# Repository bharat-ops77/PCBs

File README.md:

# Zero Voltage Switching Circuit

This is an LC tank oscillator circuit which uses two mosfets to feed the damping power to the LC tank...and use the output waveform to drive a High voltage transformer or an Induction heating coil.

---

## Repository Structure

```
├── docs/                   # Datasheet IRFP4468PbF n-channel MOSFET
├── manufacturing/          # Gerbers & BOM
│   ├── gerbers/            # Gerber and drill files for PCB fabrication
│   ├── bom/                # Bill of Materials (.csv )
├── ZVS.kicad_pcb  # KiCad PCB Layout file
├── ZVS.kicad_sch  # KiCad Schematic file
├── ZVS.kicad_pro  # KiCad Project file
└── README.md               # This file
 #Zero Voltage Switching (ZVS) Flyback Driver/Induction Heater
 ```
 This repository contains a KiCad schematic and PCB design for a high-efficiency Mazzilli Zero Voltage Switching (ZVS) Driver. This circuit is widely used for driving high-voltage transformers (like television flybacks), induction heaters, and Tesla coils due to its simplicity, high efficiency, and minimal thermal generation.
 
## **Features**:
  
  Zero Voltage Switching: The MOSFETs switch states only when the voltage across them drops to zero, drastically reducing switching losses and keeping the transistors cool.High-Current Handling: Utilizes heavy-duty IRFP4468PbF N-channel MOSFETs.Robust Gate Protection: Features dual $ Zener diodes and  pull-up resistors to prevent gate overvoltage and ensure rapid switching.
  
## **Circuit Overview & Operating Principle**:
  
  The circuit operates as a self-resonant push-pull oscillator. When power is applied via terminal J1, one MOSFET turns on slightly faster than the other. This imbalances the circuit, initiating a resonant oscillation between the parallel tank capacitors (C1 and C2) and the primary coil of the external transformer connected to J2.The fast diodes (D1 and D2) cross-couple the drains to the opposite gates, turning off one MOSFET as the other's drain voltage drops to zero.Resonant FrequencyThe operational frequency is determined solely by the total tank capacitance and the inductance of the external primary coil you attach to terminal Note: The inductors L1 and L2  act as DC chokes to smooth incoming current and do not affect the resonance frequency. Ensure your power supply can source substantial current  or more depending on your load).PCB Trace Widths: If you are routing this board, ensure the high-current paths (Power -> Input-> Chokes ->MOSFET-> Drains-> Tank ->Capacitors->Output) use very wide traces, thick copper  preferred), or are reinforced with soldered wire.Tank Capacitors: Do not use standard ceramic or cheap film capacitors for C1 and C2. The high ripple currents will quickly overheat and destroy them. Use dedicated resonant induction/MKP capacitors.Thermal Management: Even though ZVS minimizes heat, the MOSFETs will still warm up under continuous high loads. Mount both Q1 and Q2 to substantial heatsinks (isolated with mica/silicone pads if sharing a single heatsink).

## PCB Design:

   The PCB for this build is a two layer top and bottom , and uses through hole components for soldering simplicity.

## 3D Model:
### Rendered 3D Model:

### Bare PCB Front(1st Layer):  

### Bare PCB Rear(2nd Layer):  

## ⚠️WARNING:
  
  This circuit is designed to drive high-voltage/high-power components. Depending on the transformer connected to J2, it is capable of generating lethal voltages and currents. Always discharge capacitors before handling the circuit, work in a well-ventilated space, use appropriate personal protective equipment (PPE), and never operate the system unattended. The authors are not responsible for any damage, injury, or loss caused by the construction or operation of this project.
  
## 📄License:
  
  This project is open-source. Feel free to modify, distribute, and use it for your own applications under the GNU License.

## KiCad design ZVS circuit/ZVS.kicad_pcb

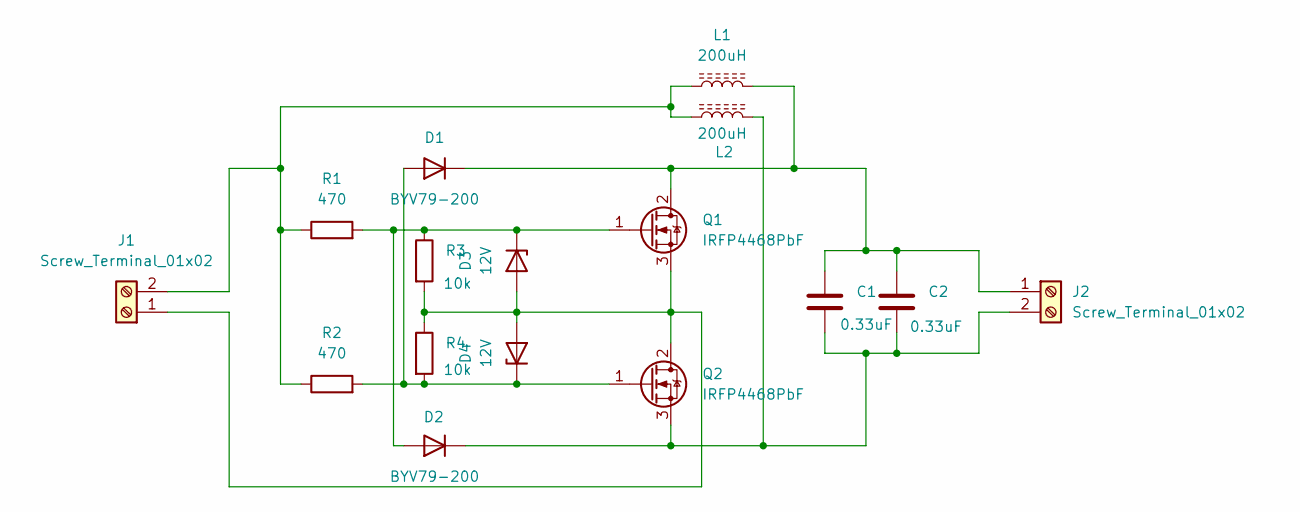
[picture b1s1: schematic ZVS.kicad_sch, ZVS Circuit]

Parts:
C1, C2: 0.33uF; C_Rect_L7.2mm_W3.0mm_P5.00mm_FKS2_FKP2_MKS2_MKP2
D1, D2: BYV79-200; TO-220-2_Vertical
D3, D4: 12V; D_A-405_P7.62mm_Horizontal
J1, J2: Screw_Terminal_01x02; TerminalBlock_MaiXu_MX126-5.0-02P_1x02_P5.00mm
L1, L2: 200uH; L_Radial_D13.5mm_P7.00mm_Fastron_09HCP
Q1, Q2: IRFP4468PbF; TO-247-3_Vertical
R1, R2: 470; R_Axial_DIN0922_L20.0mm_D9.0mm_P30.48mm_Horizontal
R3, R4: 10k; R_Axial_DIN0922_L20.0mm_D9.0mm_P30.48mm_Horizontal

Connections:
unnamed: D1.2 (A), D4.1 (K), Q2.1 (G), R2.2, R4.2
unnamed: C1.1, C2.1, D1.1 (K), J2.1, L1.2, Q1.2 (D)
unnamed: D2.2 (A), D3.1 (K), Q1.1 (G), R1.2, R3.1
unnamed: C1.2, C2.2, D2.1 (K), J2.2, L2.2, Q2.3 (S)
unnamed: D3.2 (A), D4.2 (A), J1.1, Q1.3 (S), Q2.2 (D), R3.2, R4.1
unnamed: J1.2, L1.1, L2.1, R1.1, R2.1

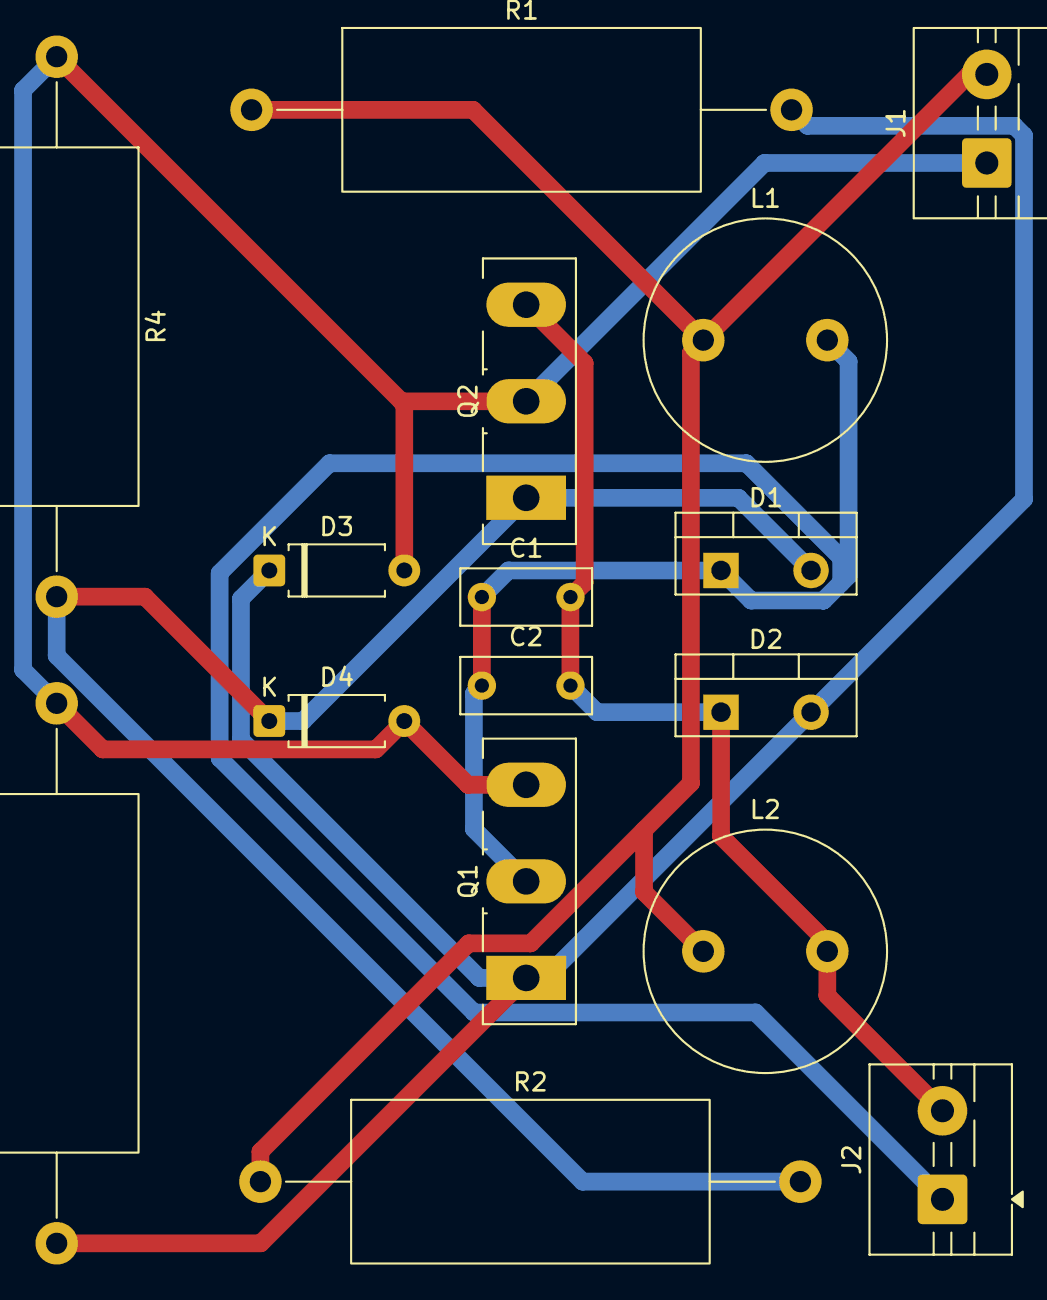
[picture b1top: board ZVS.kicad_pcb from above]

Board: 2 copper layers, 16 parts (0 on the bottom side), 6 nets.
